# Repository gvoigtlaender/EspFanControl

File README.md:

# EspFanControl
## ESP8266, DS18B20, USB-Fan, SSD1306

## Project goals:
* temperature-controlling of fan
* show status on display
* export status on mqtt
* web interface for setup
* fit into cheap USB/Lipo Fan

## Items on store:
* ESP8266 microcontroller with wifi
* DS18B20 temperature sensor
* SSD1306 OLED Display (128x64)

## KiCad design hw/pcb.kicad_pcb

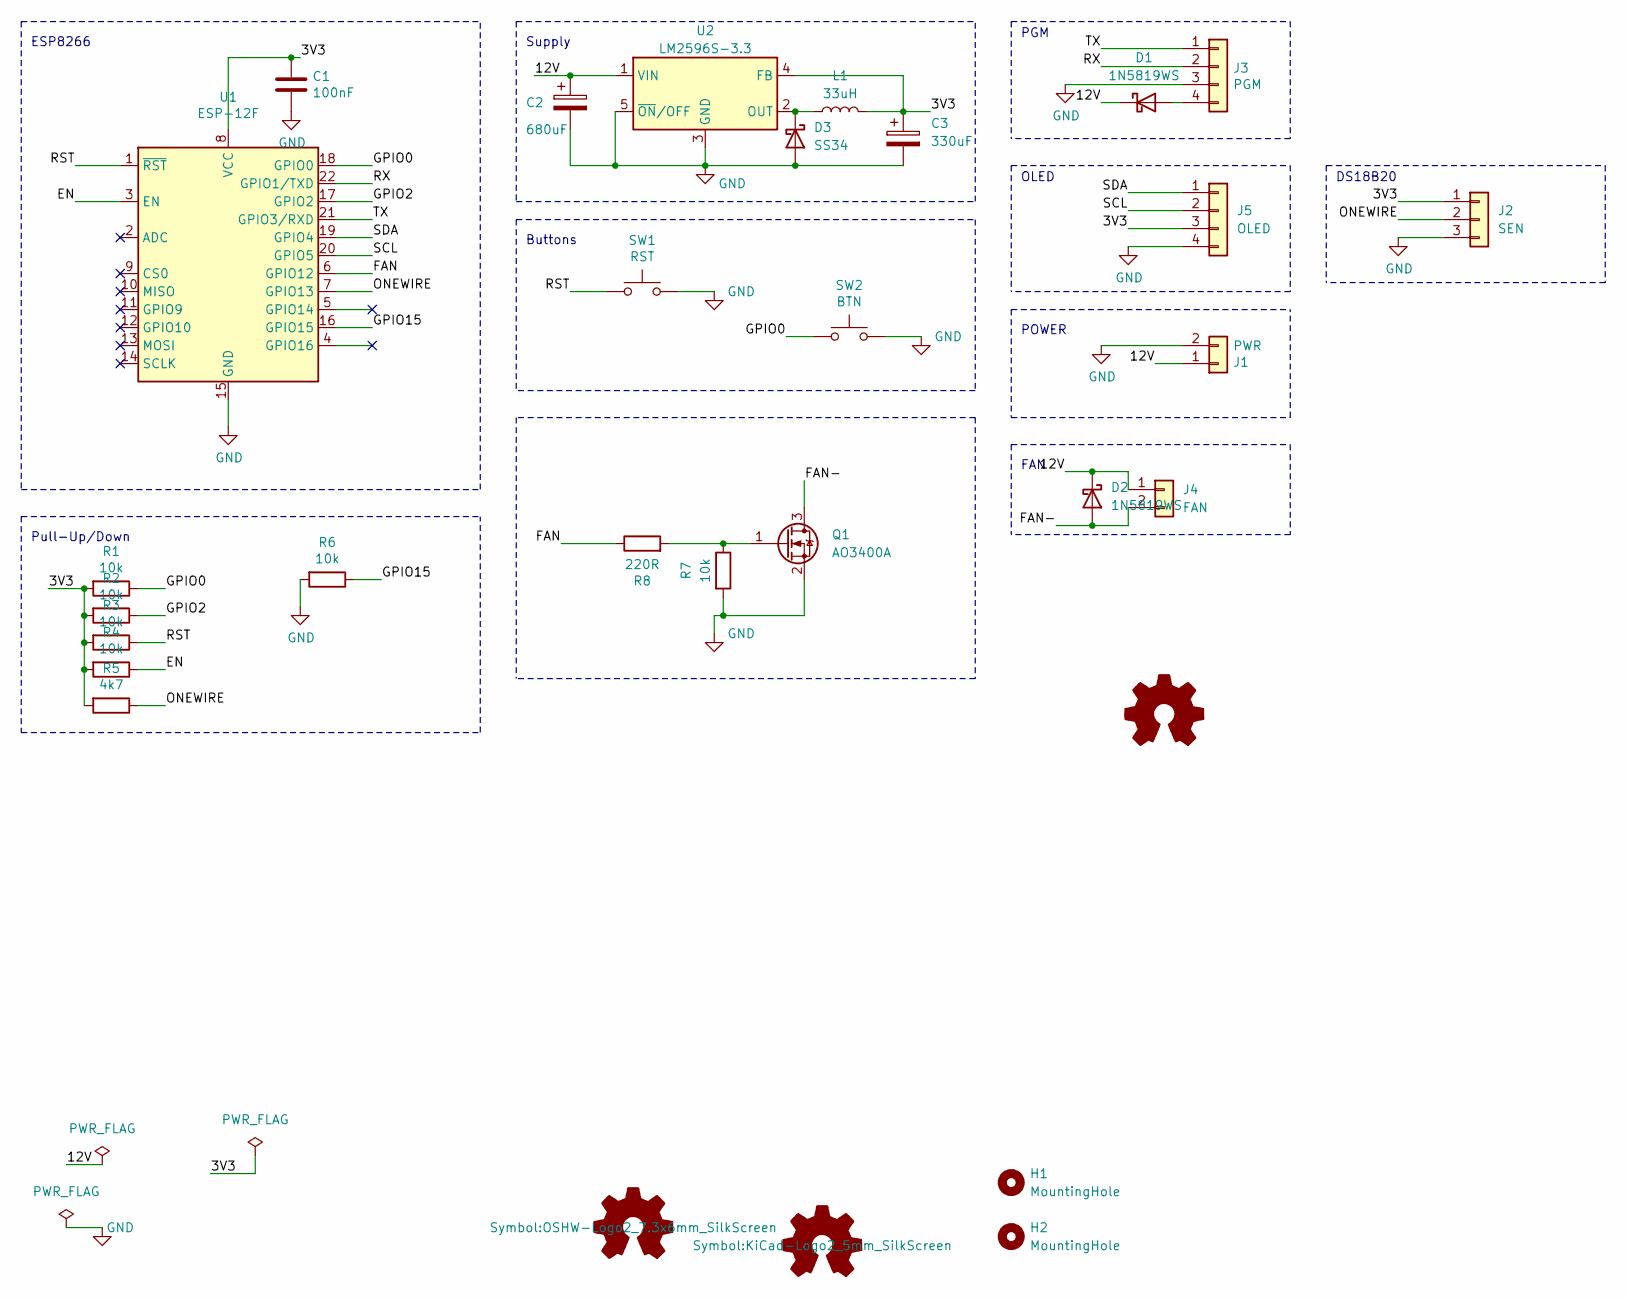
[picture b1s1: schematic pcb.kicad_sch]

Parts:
C1: 100nF; C_0805_2012Metric; LCSC C49678
C2: 680uF; CP_Radial_D4.0mm_P2.00mm
C3: 330uF; CP_EIA-7343-20_Kemet-V; LCSC C105408
D1, D2: 1N5819WS; D_SOD-323
D3: SS34; D_SMA
H1, H2: MountingHole; MountingHole_2.5mm
J1: PWR; PinHeader_1x02_P2.54mm_Vertical
J2: SEN; PinHeader_1x03_P2.54mm_Vertical
J3: PGM; JSTPH4
J4: FAN; JST-PH-2-SMT-RA
J5: OLED; PinHeader_1x04_P2.54mm_Vertical
L1: 33uH; L_12x12mm_H6mm; LCSC C339945
Q1: AO3400A; SOT-23
R1, R2, R3, R4, R6, R7: 10k; R_0603_1608Metric; LCSC C17414
R5: 4k7; R_0603_1608Metric; LCSC C17673
R8: 220R; R_0603_1608Metric; LCSC C17414
SW1: RST; SW_SPST_CK_RS282G05A3
SW2: BTN; SW_SPST_TL3342
U1: ESP-12F; ESP-12E
U2: LM2596S-3.3; TO-263-5_TabPin3; LCSC C347420

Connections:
/3V3: C1.1, C3.1, J2.1, J5.3, L1.2, R1.2, R2.2, R3.2, R4.2, R5.2, U1.8 (VCC), U2.4 (FB)
/12V: C2.1, D1.1 (K), D2.1 (K), J1.1, J4.1, U2.1 (VIN)
/EN: R4.1, U1.3 (EN)
/FAN: R8.1, U1.6 (GPIO12)
/FAN-: D2.2 (A), J4.2, Q1.3 (D)
/GPIO0: R1.1, SW2.1, U1.18 (GPIO0)
/GPIO2: R2.1, U1.17 (GPIO2)
/GPIO15: R6.1, U1.16 (GPIO15)
/ONEWIRE: J2.2, R5.1, U1.7 (GPIO13)
/RST: R3.1, SW1.1, U1.1 (~RST)
/RX: J3.2, U1.22 (GPIO1/TXD)
/SCL: J5.2, U1.20 (GPIO5)
/SDA: J5.1, U1.19 (GPIO4)
/TX: J3.1, U1.21 (GPIO3/RXD)
GND: C1.2, C2.2, C3.2, D3.2 (A), J1.2, J2.3, J3.3, J5.4, Q1.2 (S), R6.2, R7.2, SW1.2, SW2.2, U1.15 (GND), U2.3 (GND), U2.5 (~ON/OFF)
unnamed: D1.2 (A), J3.4
unnamed: D3.1 (K), L1.1, U2.2 (OUT)
unnamed: Q1.1 (G), R7.1, R8.2

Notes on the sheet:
FAN
ESP8266
DS18B20
Buttons
Supply
POWER
OLED
PGM
Pull-Up/Down

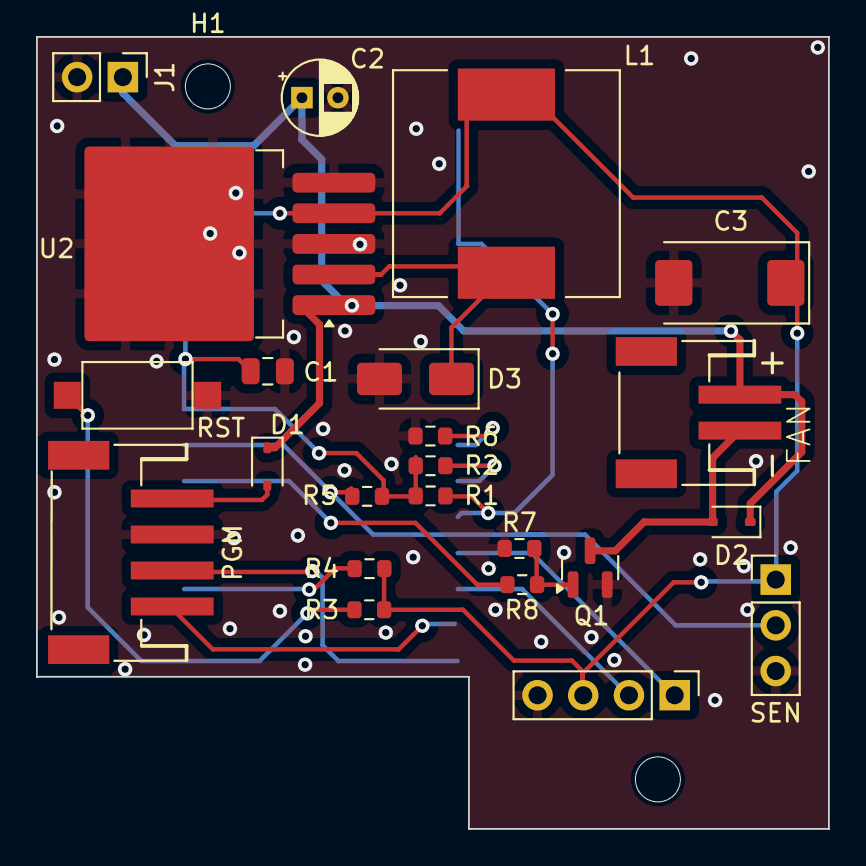
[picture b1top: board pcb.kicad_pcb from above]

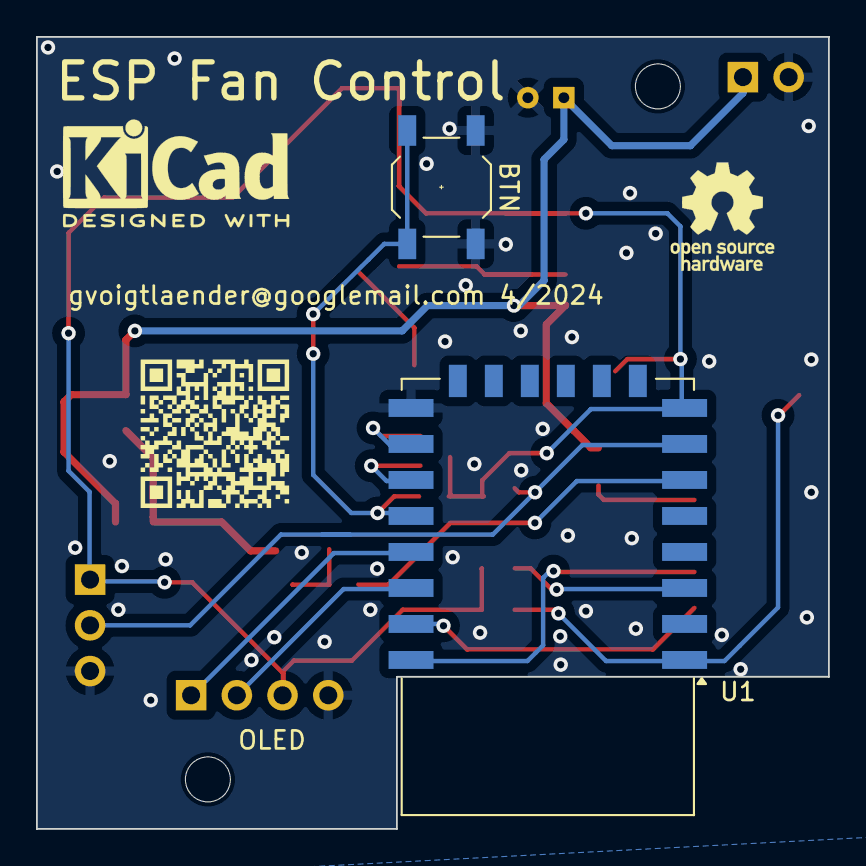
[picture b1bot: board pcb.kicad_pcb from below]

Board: 2 copper layers, 44.0 x 44.0 mm, 28 parts (3 on the bottom side), 18 nets.

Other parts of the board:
QR*****: qr_espfc

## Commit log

2022-12-23 add hw
2023-01-22 update: cleanup
2023-06-15 update(mqtt): FanStateB, OnOff as double, Temperature
2023-07-06 add scope to display
2023-07-06 add scope
2023-10-15 test
2023-10-15 sub dir
2024-03-17 display raw temp
2024-03-25 add CI script
2024-03-25 mvoe CI script
2024-05-12 wifi defaults
2024-05-12 update actions
2024-05-13 add esp12e5v
2024-05-13 add hw_5v
2025-06-04 xbm graph
2025-06-05 display hover line
2025-06-30 keep display alive on long click
